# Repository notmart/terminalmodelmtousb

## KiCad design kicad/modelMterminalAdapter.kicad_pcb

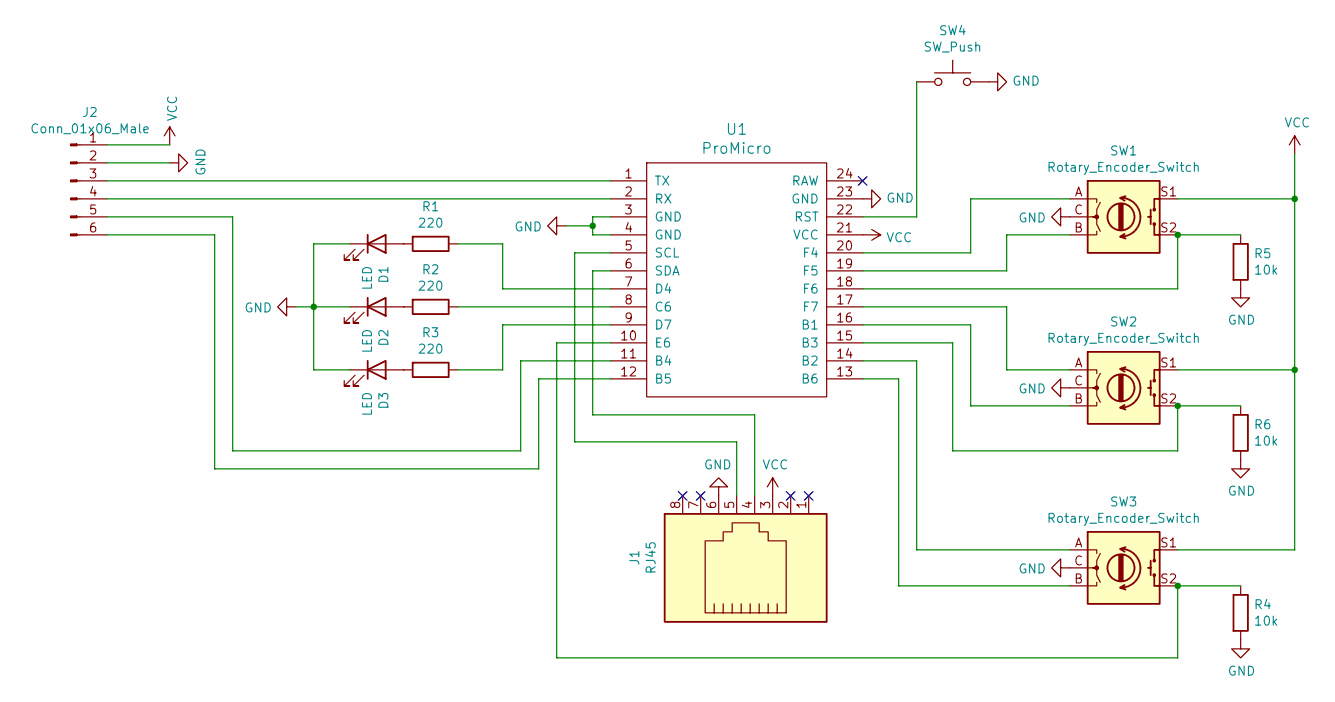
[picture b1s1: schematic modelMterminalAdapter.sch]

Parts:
D1, D2, D3: LED; LED_D5.0mm
J1: RJ45; RJ45_Amphenol_RJHSE5380
J2: Conn_01x06_Male; PinHeader_1x06_P2.54mm_Vertical
R1, R2, R3: 220; R_Axial_DIN0207_L6.3mm_D2.5mm_P7.62mm_Horizontal
R4, R5, R6: 10k; R_Axial_DIN0207_L6.3mm_D2.5mm_P7.62mm_Horizontal
SW1, SW2, SW3: Rotary_Encoder_Switch; RotaryEncoder_Alps_EC11E-Switch_Vertical_H20mm
SW4: SW_Push; SW_SPST_CK_RS282G05A3
U1: ProMicro

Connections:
GND: D1.1 (K), D2.1 (K), D3.1 (K), J1.6, J2.2, R4.2, R5.2, R6.2, SW1.C, SW2.C, SW3.C, SW4.2, U1.3 (GND), U1.4 (GND), U1.23 (GND)
unnamed: D1.2 (A), R1.2
unnamed: D2.2 (A), R2.2
unnamed: D3.2 (A), R3.2
unnamed: J1.4, U1.6 (SDA)
unnamed: J1.5, U1.5 (SCL)
unnamed: J2.3, U1.1 (TX)
unnamed: J2.4, U1.2 (RX)
unnamed: J2.5, U1.11 (B4)
unnamed: J2.6, U1.12 (B5)
unnamed: R1.1, U1.7 (D4)
unnamed: R2.1, U1.8 (C6)
unnamed: R3.1, U1.9 (D7)
unnamed: R4.1, SW3.S2, U1.10 (E6)
unnamed: R5.1, SW1.S2, U1.18 (F6)
unnamed: R6.1, SW2.S2, U1.15 (B3)
unnamed: SW1.A, U1.20 (F4)
unnamed: SW1.B, U1.19 (F5)
unnamed: SW2.A, U1.17 (F7)
unnamed: SW2.B, U1.16 (B1)
unnamed: SW3.A, U1.14 (B2)
unnamed: SW3.B, U1.13 (B6)
unnamed: SW4.1, U1.22 (RST)
VCC: J1.3, J2.1, SW1.S1, SW2.S1, SW3.S1, U1.21 (VCC)

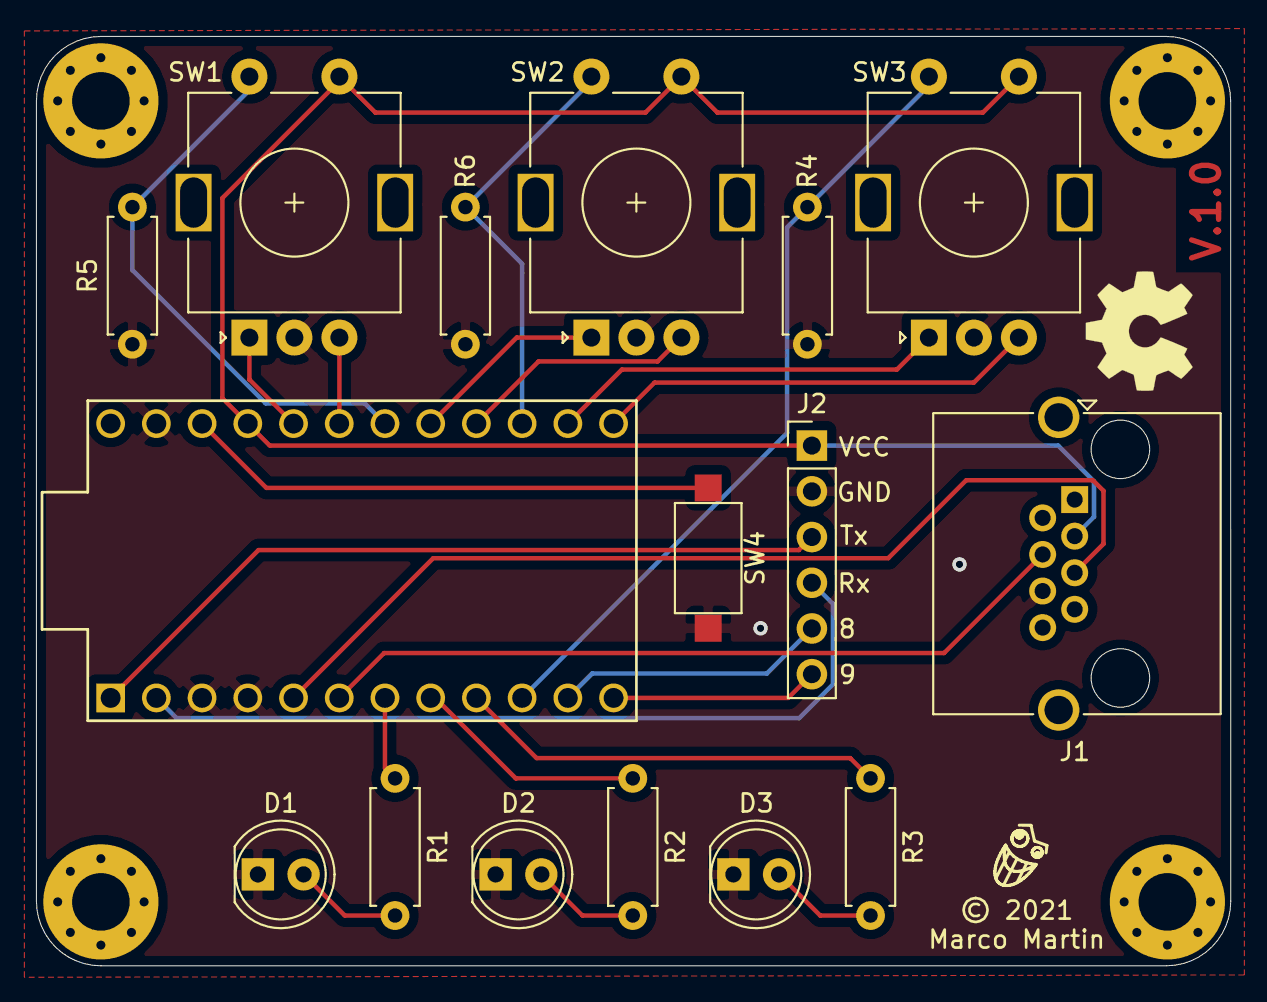
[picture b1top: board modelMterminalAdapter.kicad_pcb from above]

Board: 2 copper layers, 66.4 x 51.6 mm, 20 parts (0 on the bottom side), 24 nets.

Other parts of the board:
mount1, mount2, mount3, mount4: MountingHole_3.2mm_M3_Pad_Via

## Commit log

2021-03-27 initial code commit
2021-05-25 add basic support for a rotary encoder
2021-05-25 add a Kicad project for a pcb based on pro micro
2021-05-25 add open hardware license
2021-05-25 library for a basic polling-based encoder
2021-06-11 support for polling button presses
2021-06-11 simple macro support
2021-06-11 update 3d model
2021-06-25 update the led pins
2022-01-19 add software debounce for encoder buttons

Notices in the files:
kicad/modelMterminalAdapter.kicad_pcb:
© 2021
